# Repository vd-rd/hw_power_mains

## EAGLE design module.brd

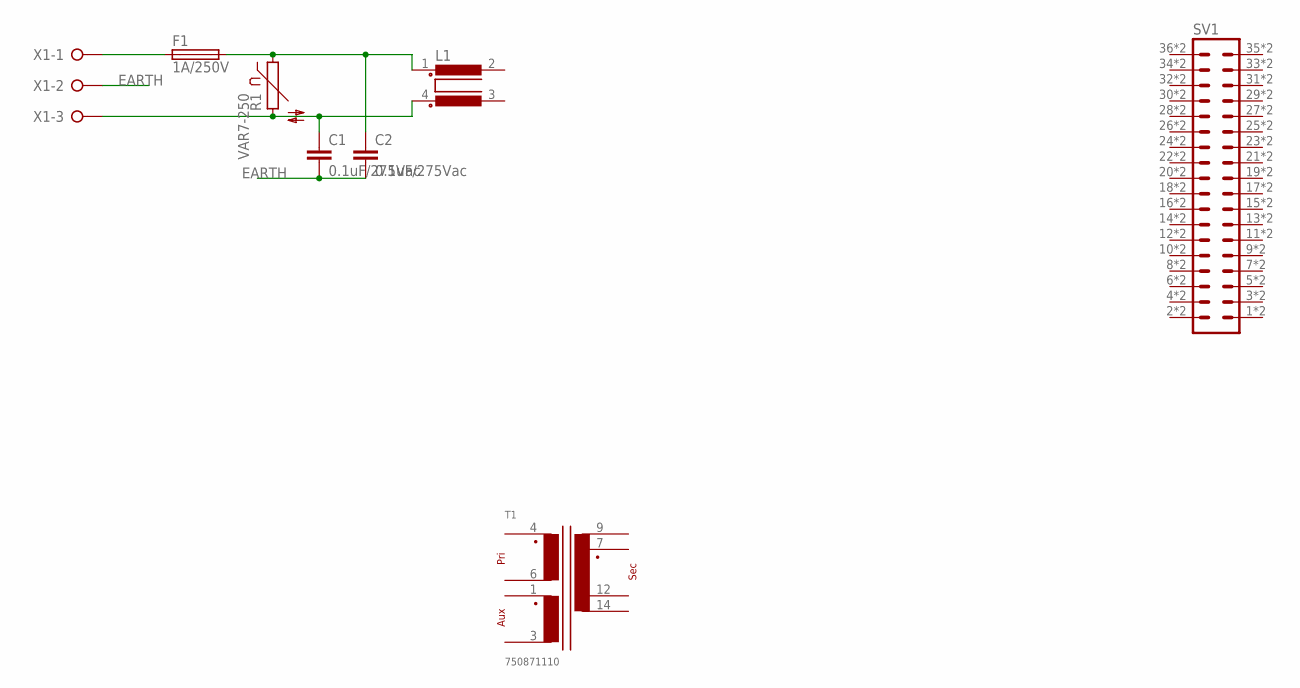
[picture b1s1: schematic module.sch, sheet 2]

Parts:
C1, C2: 0.1uF/275Vac; C102-064X133
F1: 1A/250V; ZH8X2
L1: SSR7HS-M11064; SSRH7HS-M
R1: VAR7-250; S05K250
SV1: MA18-2SMT; MA18-2-SMT
T1: 750871110; EE20/9/11_THT_H_14PIN_EXT_(5443)
X1: W237-03P; W237-133

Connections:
EARTH: C1.2, C2.2, X1.2
unnamed: F1.1, F1.1A (1), X1.1
unnamed: C1.1, L1.4, R1.2, X1.3
unnamed: C2.1, F1.2, F1.2A (2), L1.1, R1.1

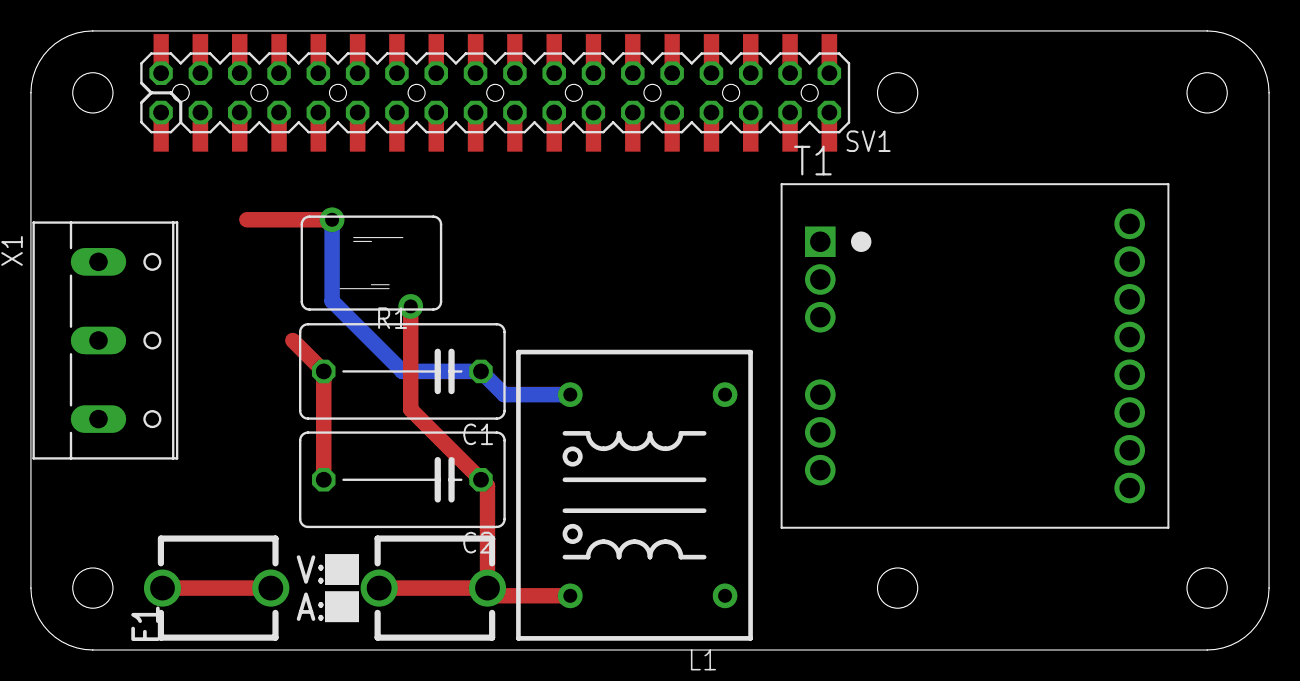
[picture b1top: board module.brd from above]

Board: 2 copper layers, 80.0 x 40.0 mm, 8 parts (0 on the bottom side), 4 nets.

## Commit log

2019-08-12 project: added layout files
2019-08-19 project: defined mains filter
2019-09-24 project: add embedded connector
